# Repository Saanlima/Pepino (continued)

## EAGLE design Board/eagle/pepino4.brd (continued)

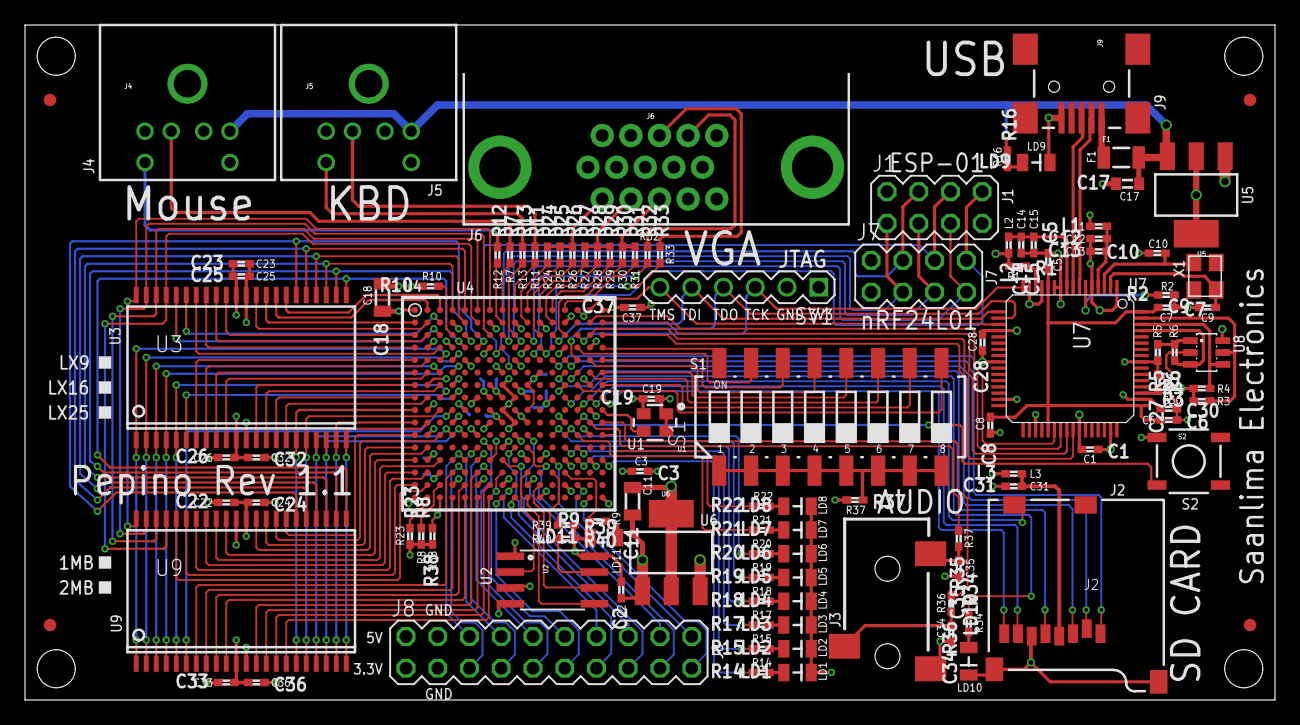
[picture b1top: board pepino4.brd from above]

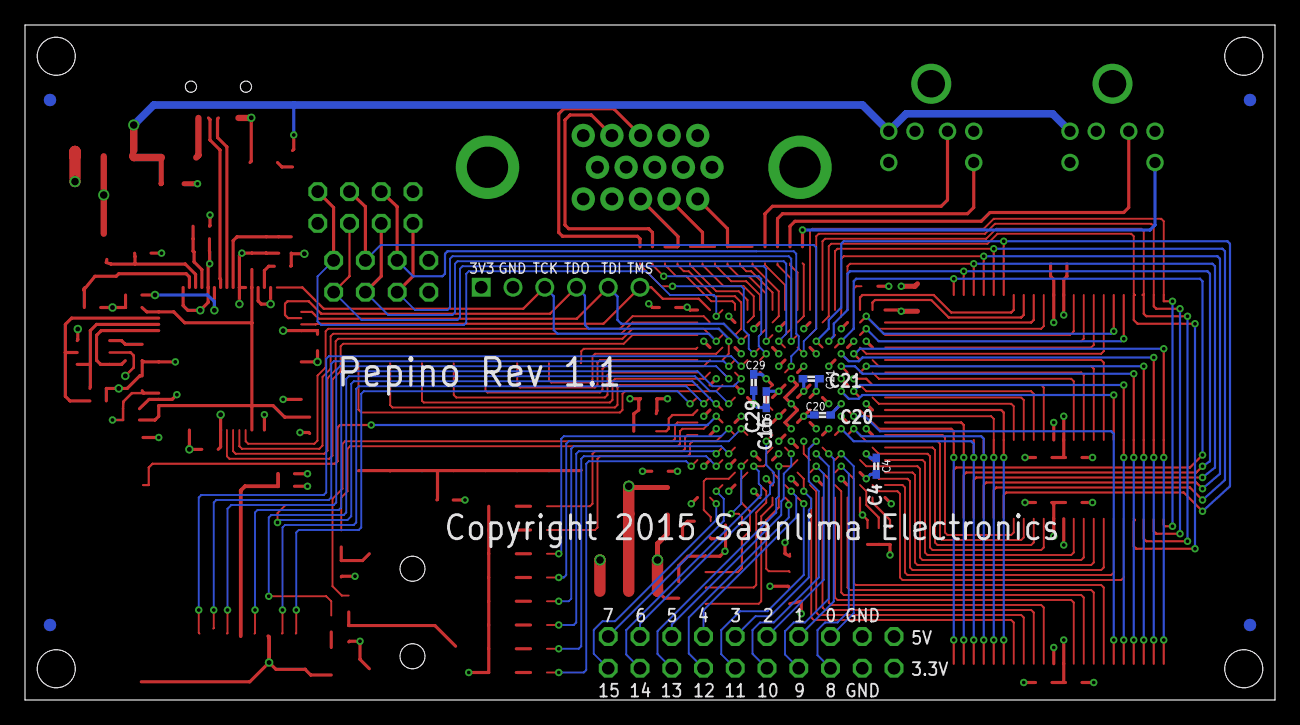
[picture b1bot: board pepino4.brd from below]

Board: 4 copper layers, 100.0 x 54.0 mm, 122 parts (9 on the bottom side), 183 nets.

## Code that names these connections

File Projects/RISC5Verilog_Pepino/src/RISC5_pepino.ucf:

NET "*" IOSTANDARD=LVCMOS33;
CONFIG VCCAUX = "3.3" ;

NET "CLK50M" LOC = "J16";
NET "CLK50M" TNM_NET = "osc";
TIMESPEC "TS_osc" = PERIOD "osc" 20.000ns;

NET "TxD" LOC = "B16";
NET "RxD" LOC = "B15";

NET "btn[0]" LOC = "P5" | PULLDOWN; #IO1N
NET "btn[1]" LOC = "N6" | PULLDOWN; #IO2N
NET "btn[2]" LOC = "M7" | PULLDOWN; #IO3N
NET "btn[3]" LOC = "T8" | PULLDOWN; #IO4N

NET "swi[0]" LOC = "G14" | PULLDOWN;
NET "swi[1]" LOC = "G16" | PULLDOWN;
NET "swi[2]" LOC = "F15" | PULLDOWN;
NET "swi[3]" LOC = "F16" | PULLDOWN;
NET "swi[4]" LOC = "E15" | PULLDOWN;
NET "swi[5]" LOC = "E16" | PULLDOWN;
NET "swi[6]" LOC = "D14" | PULLDOWN;
NET "swi[7]" LOC = "D16" | PULLDOWN;

NET "leds[0]" LOC = "N16";
NET "leds[1]" LOC = "N14";
NET "leds[2]" LOC = "M14";
NET "leds[3]" LOC = "M13";
NET "leds[4]" LOC = "L12";
NET "leds[5]" LOC = "L13";
NET "leds[6]" LOC = "L14";
NET "leds[7]" LOC = "L16";

NET "SDled" LOC = "H13";

# SRAM
NET "SRce0" LOC = "H4";
NET "SRce1" LOC = "J4";
NET "SRwe" LOC = "J1";
NET "SRoe" LOC = "B6";
NET "SRbe[0]" LOC = "B3";
NET "SRbe[1]" LOC = "C3";
NET "SRbe[2]" LOC = "R1";
NET "SRbe[3]" LOC = "R2";
NET "SRadr[0]" LOC = "E3";
NET "SRadr[1]" LOC = "E4";
NET "SRadr[2]" LOC = "F3";
NET "SRadr[3]" LOC = "F4";
NET "SRadr[4]" LOC = "H3";
NET "SRadr[5]" LOC = "J3";
NET "SRadr[6]" LOC = "L4";
NET "SRadr[7]" LOC = "L5";
NET "SRadr[8]" LOC = "K1";
NET "SRadr[9]" LOC = "K2";
NET "SRadr[10]" LOC = "D5";
NET "SRadr[11]" LOC = "C5";
NET "SRadr[12]" LOC = "A4";
NET "SRadr[13]" LOC = "B5";
NET "SRadr[14]" LOC = "A5";
NET "SRadr[15]" LOC = "A6";
NET "SRadr[16]" LOC = "C7";
NET "SRadr[17]" LOC = "A7";
NET "SRadr[18]" LOC = "D6";
NET "SRdat[0]" LOC = "E1";
NET "SRdat[1]" LOC = "E2";
NET "SRdat[2]" LOC = "F1";
NET "SRdat[3]" LOC = "F2";
NET "SRdat[4]" LOC = "G1";
NET "SRdat[5]" LOC = "G3";
NET "SRdat[6]" LOC = "H1";
NET "SRdat[7]" LOC = "H2";
NET "SRdat[8]" LOC = "A3";
NET "SRdat[9]" LOC = "A2";
NET "SRdat[10]" LOC = "B1";
NET "SRdat[11]" LOC = "B2";
NET "SRdat[12]" LOC = "C1";
NET "SRdat[13]" LOC = "C2";
NET "SRdat[14]" LOC = "D1";
NET "SRdat[15]" LOC = "D3";
NET "SRdat[16]" LOC = "P4";
NET "SRdat[17]" LOC = "T4";
NET "SRdat[18]" LOC = "R5";
NET "SRdat[19]" LOC = "T5";
NET "SRdat[20]" LOC = "P6";
NET "SRdat[21]" LOC = "T6";
NET "SRdat[22]" LOC = "R7";
NET "SRdat[23]" LOC = "T7";
NET "SRdat[24]" LOC = "L1";
NET "SRdat[25]" LOC = "L3";
NET "SRdat[26]" LOC = "M1";
NET "SRdat[27]" LOC = "M2";
NET "SRdat[28]" LOC = "N1";
NET "SRdat[29]" LOC = "N3";
NET "SRdat[30]" LOC = "P1";
NET "SRdat[31]" LOC = "P2";

# VGA port
NET "Hsync"  LOC = "D11";
NET "Vsync"  LOC = "E11";
NET "RGB[0]" LOC = "B10"; # RED 0
NET "RGB[1]" LOC = "A10"; # RED 1
NET "RGB[2]" LOC = "C11"; # RED 2
NET "RGB[3]" LOC = "A11"; # GREEN 0
NET "RGB[4]" LOC = "B12"; # GREEN 1
NET "RGB[5]" LOC = "A12"; # GREEN 2
NET "RGB[6]" LOC = "C13"; # BLUE 0
NET "RGB[7]" LOC = "A13"; # BLUE 1

# PS/2 keyboard
NET "PS2C" LOC = "C9" | PULLUP;
NET "PS2D" LOC = "A9" | PULLUP;

# PS/2 mouse
NET "msclk" LOC = "B8" | PULLUP;
NET "msdat" LOC = "A8" | PULLUP;

# SPI (SD-Card and Network)
NET "MOSI[0]" LOC = "F14";
NET "MOSI[1]" LOC = "D8";
NET "SCLK[0]" LOC = "F13";
NET "SCLK[1]" LOC = "D9";
NET "SS[0]" LOC = "E13";
NET "SS[1]" LOC = "F9";
NET "MISO[0]" LOC = "H15" | PULLUP;
NET "MISO[1]" LOC = "C10" | PULLUP;
NET "NEN" LOC = "C8";

# general-purpose I/O port
NET "gpio[0]" LOC = "N5"; #IO1P
NET "gpio[1]" LOC = "M6"; #IO2P
NET "gpio[2]" LOC = "P7"; #IO3P
NET "gpio[3]" LOC = "P8"; #IO4P
NET "gpio[4]" LOC = "R9"; #IO5P
NET "gpio[5]" LOC = "M9"; #IO6P
NET "gpio[6]" LOC = "L10"; #IO7P
NET "gpio[7]" LOC = "R14"; #IO8P

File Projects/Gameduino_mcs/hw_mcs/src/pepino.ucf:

CONFIG VCCAUX = "3.3" ;

# ==== Clock inputs (CLK) ====
NET "CLK_50MHZ" LOC = "J16"  | IOSTANDARD = LVCMOS33;
NET "CLK_50MHZ" TNM_NET = sys_clk_pin;
TIMESPEC TS_sys_clk_pin = PERIOD sys_clk_pin 50000 kHz;

# ==== Pushbuttons (BTN) ====
NET "SWITCH"        LOC = K14 | IOSTANDARD = LVCMOS33 | PULLDOWN; #SWITCH

# FTDI FT2232-chB used as USB UART
NET "txd"        LOC = "B16"  | IOSTANDARD = LVCMOS33 | DRIVE = 8 | SLEW = FAST ;
NET "rxd"        LOC = "B15"  | IOSTANDARD = LVCMOS33 | PULLUP;

# ==== Audio ====
NET "AUDIO_LEFT"  LOC = "K15" | IOSTANDARD = LVCMOS33 | SLEW = SLOW | DRIVE = 6;
NET "AUDIO_RIGHT" LOC = "K16" | IOSTANDARD = LVCMOS33 | SLEW = SLOW | DRIVE = 6;

# === VGA port ===
NET "VGA_HSYNC"    LOC = D11 | IOSTANDARD = LVCMOS33;
NET "VGA_VSYNC"    LOC = E11 | IOSTANDARD = LVCMOS33;
NET "VGA_RED<0>"   LOC = B10 | IOSTANDARD = LVCMOS33;
NET "VGA_RED<1>"   LOC = A10 | IOSTANDARD = LVCMOS33;
NET "VGA_RED<2>"   LOC = C11 | IOSTANDARD = LVCMOS33;
NET "VGA_GREEN<0>" LOC = A11 | IOSTANDARD = LVCMOS33;
NET "VGA_GREEN<1>" LOC = B12 | IOSTANDARD = LVCMOS33;
NET "VGA_GREEN<2>" LOC = A12 | IOSTANDARD = LVCMOS33;
NET "VGA_BLUE<0>"  LOC = C13 | IOSTANDARD = LVCMOS33;
NET "VGA_BLUE<1>"  LOC = A13 | IOSTANDARD = LVCMOS33;

# ==== sd-card SPI interface ====
NET "SD_MISO"   LOC = "H15"   | IOSTANDARD = SDIO | SLEW = FAST | DRIVE = 8 | PULLUP ;
NET "SD_CS"     LOC = "E13"   | IOSTANDARD = SDIO | SLEW = FAST | DRIVE = 8 | PULLUP ;
NET "SD_MOSI"   LOC = "F14"   | IOSTANDARD = SDIO | SLEW = FAST | DRIVE = 8 | PULLUP ;
NET "SD_SCK"    LOC = "F13"   | IOSTANDARD = SDIO | SLEW = FAST | DRIVE = 8 ;

# ==== LEDs ====
NET "LED1"      LOC = "N16"  | IOSTANDARD = LVCMOS33 | SLEW = SLOW | DRIVE = 8 ;
NET "LED2"      LOC = "N14"  | IOSTANDARD = LVCMOS33 | SLEW = SLOW | DRIVE = 8 ;
NET "LED3"      LOC = "M14"  | IOSTANDARD = LVCMOS33 | SLEW = SLOW | DRIVE = 8 ;
NET "LED4"      LOC = "M13"  | IOSTANDARD = LVCMOS33 | SLEW = SLOW | DRIVE = 8 ;
NET "LED5"      LOC = "H13"  | IOSTANDARD = LVCMOS33 | SLEW = SLOW | DRIVE = 8 ;

# ==== Wings ====
NET WING_A[15]  LOC = "T15" | IOSTANDARD = LVCMOS33 | DRIVE = 8 | SLEW = FAST | PULLDOWN ;
NET WING_A[14]  LOC = "M10" | IOSTANDARD = LVCMOS33 | DRIVE = 8 | SLEW = FAST | PULLDOWN ;
NET WING_A[13]  LOC = "N8"  | IOSTANDARD = LVCMOS33 | DRIVE = 8 | SLEW = FAST | PULLDOWN ;
NET WING_A[12]  LOC = "T9"  | IOSTANDARD = LVCMOS33 | DRIVE = 8 | SLEW = FAST | PULLDOWN ;
NET WING_A[11]  LOC = "T8"  | IOSTANDARD = LVCMOS33 | DRIVE = 8 | SLEW = FAST | PULLDOWN ;
NET WING_A[10]  LOC = "M7"  | IOSTANDARD = LVCMOS33 | DRIVE = 8 | SLEW = FAST | PULLDOWN ;
NET WING_A[9]   LOC = "N6"  | IOSTANDARD = LVCMOS33 | DRIVE = 8 | SLEW = FAST | PULLDOWN ;
NET WING_A[8]   LOC = "P5"  | IOSTANDARD = LVCMOS33 | DRIVE = 8 | SLEW = FAST | PULLDOWN ;
NET WING_A[7]   LOC = "R14" | IOSTANDARD = LVCMOS33 | DRIVE = 8 | SLEW = FAST | PULLDOWN ;
NET WING_A[6]   LOC = "L10" | IOSTANDARD = LVCMOS33 | DRIVE = 8 | SLEW = FAST | PULLDOWN ;
NET WING_A[5]   LOC = "M9"  | IOSTANDARD = LVCMOS33 | DRIVE = 8 | SLEW = FAST | PULLDOWN ;
NET WING_A[4]   LOC = "R9"  | IOSTANDARD = LVCMOS33 | DRIVE = 8 | SLEW = FAST | PULLDOWN ;
NET WING_A[3]   LOC = "P8"  | IOSTANDARD = LVCMOS33 | DRIVE = 8 | SLEW = FAST | PULLDOWN ;
NET WING_A[2]   LOC = "P7"  | IOSTANDARD = LVCMOS33 | DRIVE = 8 | SLEW = FAST | PULLDOWN ;
NET WING_A[1]   LOC = "M6"  | IOSTANDARD = LVCMOS33 | DRIVE = 8 | SLEW = FAST | PULLDOWN ;
NET WING_A[0]   LOC = "N5"  | IOSTANDARD = LVCMOS33 | DRIVE = 8 | SLEW = FAST | PULLDOWN ;

NET SPI_FLASH_HOLDn  LOC = "P12"  |  IOSTANDARD = LVCMOS33;
NET SPI_FLASH_MISO   LOC = "P10"  |  IOSTANDARD = LVCMOS33;
NET SPI_FLASH_MOSI   LOC = "T10"  |  IOSTANDARD = LVCMOS33;
NET SPI_FLASH_SCLK   LOC = "R11"  |  IOSTANDARD = LVCMOS33;
NET SPI_FLASH_SS     LOC = "T3"   |  IOSTANDARD = LVCMOS33;
NET SPI_FLASH_Wn     LOC = "N12"  |  IOSTANDARD = LVCMOS33;

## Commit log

2016-02-12 Adding ISE project
2016-02-12 Adding more ISE projects
2016-02-12 Adding Pepino_waveplayer
2016-02-12 Fixed the path to the bit file
2016-02-13 Updated the README file
2016-02-16 Added project
2016-02-18 Updated the design to be fully synchronous
2016-02-18 Clean-up (no functional changes)
2016-02-19 Backing out the changes to make is synchronous
2016-02-19 Changed the clock generation to use a DCM
2016-02-24 Updated the code to use DDR output driver for write enable
2016-02-26 Fast version of Oberon for Pepino added
2016-02-26 Added README, misc cleanup
2016-02-26 Fixed typos in the README file
2016-02-26 Fixed typos
2016-02-29 Multiplier changed to only take 1 clk vs. 16 clk in the original code
2016-03-01 Added instance names
2016-03-02 Switched over to use MouseM.v
2016-03-28 Added RISC5Verilog_Pepino_I2C
2016-04-01 Added more documentation
2016-04-03 Added UART_echo project
2016-04-03 Added bit file
2016-04-11 Added Snake project
2016-04-11 Removed tabs
2016-04-11 Updated the README, fixed some typos
2016-04-23 Removed RISC5Verilog_Pepino_fast
2016-04-23 RISC5Verilog_Pepino_RGB added
2016-04-24 Added license.txt
2016-05-06 Added 37.5 MHz version of Oberon for Pepino
2020-05-03 Added board files
2020-05-03 Removed non-functional project
